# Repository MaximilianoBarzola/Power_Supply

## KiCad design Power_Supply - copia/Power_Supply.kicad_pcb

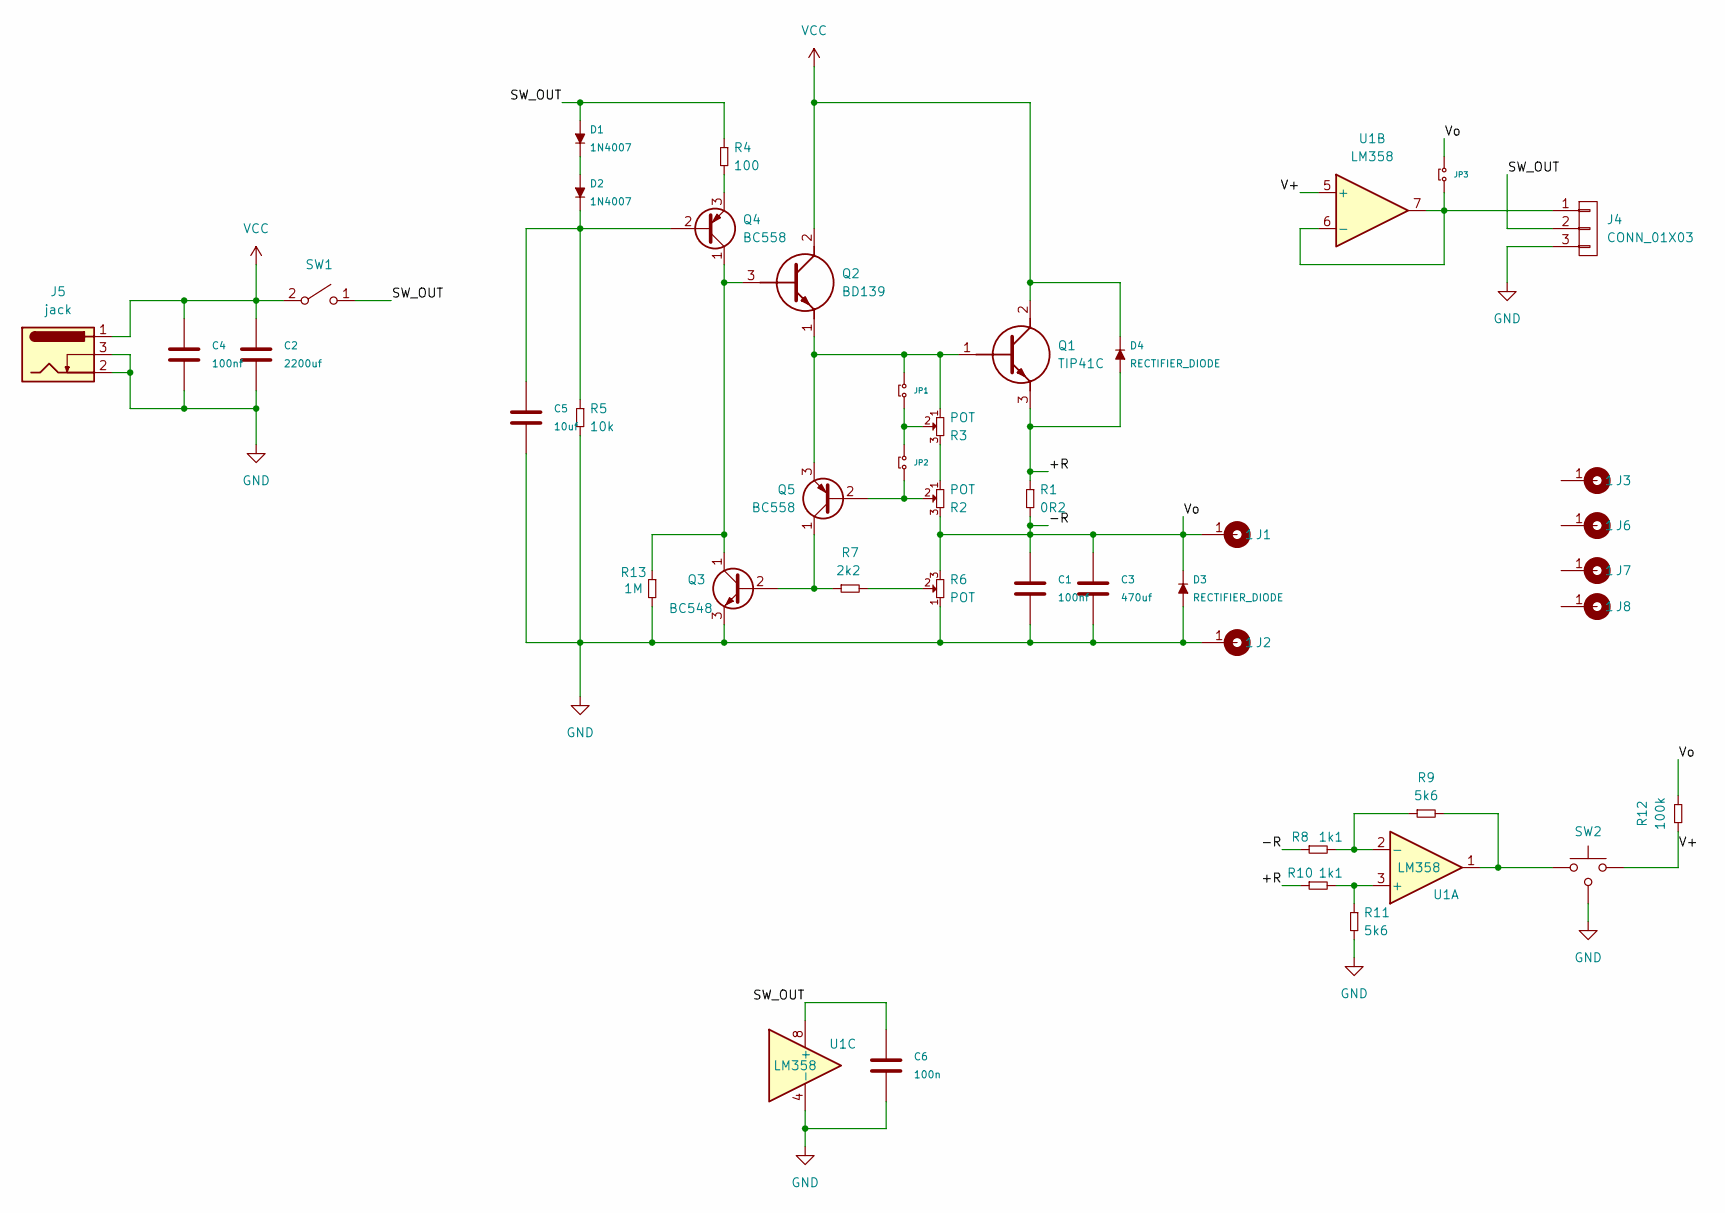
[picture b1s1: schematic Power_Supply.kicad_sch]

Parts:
C1, C4: 100nf; C_POL
C2: 2200uf; C_ELEC_15x12
C3: 470uf; C-ELEC
C5: 10uf; CAP_ELEC_5x11mm
C6: 100n; C_POL
D1, D2: 1N4007; DO-41
D3, D4: RECTIFIER_DIODE; DO-41
J1, J2: Cable_PAD; Cable_1,5mm
J3, J6, J7, J8: Cable_PAD; Separador_M3_10mm
J4: CONN_01X03; Pin_Header_3
J5: jack; Jack_hembra_DC_barrel
JP1, JP2, JP3: Jumper; JUMPER
Q1: TIP41C; TO-220-3_90; Manufacturer_Part_Number TIP41C; Mouser Part Number 512-TIP41C
Q2: BD139; TO-126-3_90; Manufacturer_Part_Number BD139; Mouser Part Number 863-BD139
Q3: BC548; to92
Q4, Q5: BC558; to92; Manufacturer_Part_Number BC558; Mouser Part Number 512-BC558
R1: 0R2; RESO_2W
R2, R6: POT; Pin_Header_3
R3: POT; TRIMER_V
R4: 100; RES0.3
R5: 10k; RES0.3
R7: 2k2; RES0.3
R8, R10: 1k1; RES0.3
R9, R11: 5k6; RES0.3
R12: 100k; RES0.3
R13: 1M; RES0.3
SW1: SW_SPST; Pin_Header_2
SW2: SW_Push; PUSH_SWITCH_THT_90
U1: LM358; DIP-8

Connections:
/+R: D4.1 (A), Q1.3 (E), R1.1, R10.1
/-R: C1.1, C3.1, D3.2 (K), J1.1, JP3.1 (A), R1.2, R2.3, R6.3, R8.1, R12.2
/SW_OUT: C6.1, D1.1 (A), J4.2, R4.1, SW1.1 (A), U1.8 (+)
/V+: R12.1, SW2.1, U1.5 (+)
GND: C1.2, C2.2, C3.2, C4.2, C5.2, C6.2, D3.1 (A), J2.1, J4.3, J5.2, J5.3, Q3.3 (E), R5.2, R6.1, R11.2, R13.2, SW2.3, U1.4 (-)
unnamed: D1.2 (K), D2.1 (A)
unnamed: C5.1, D2.2 (K), Q4.2 (B), R5.1
unnamed: J4.1, JP3.2 (B), U1.6 (-), U1.7
unnamed: JP1.1 (A), Q1.1 (B), Q2.1 (E), Q5.3 (E), R3.1
unnamed: JP1.2 (B), JP2.1 (A), R3.2
unnamed: JP2.2 (B), Q5.2 (B), R2.2
unnamed: Q2.3 (B), Q3.1 (C), Q4.1 (C), R13.1
unnamed: Q3.2 (B), Q5.1 (C), R7.1
unnamed: Q4.3 (E), R4.2
unnamed: R2.1, R3.3
unnamed: R6.2, R7.2
unnamed: R9.2, SW2.2, U1.1
unnamed: R10.2, R11.1, U1.3 (+)
unnamed: R8.2, R9.1, U1.2 (-)
VCC: C2.1, C4.1, D4.2 (K), J5.1, Q1.2 (C), Q2.2 (C), SW1.2 (B)

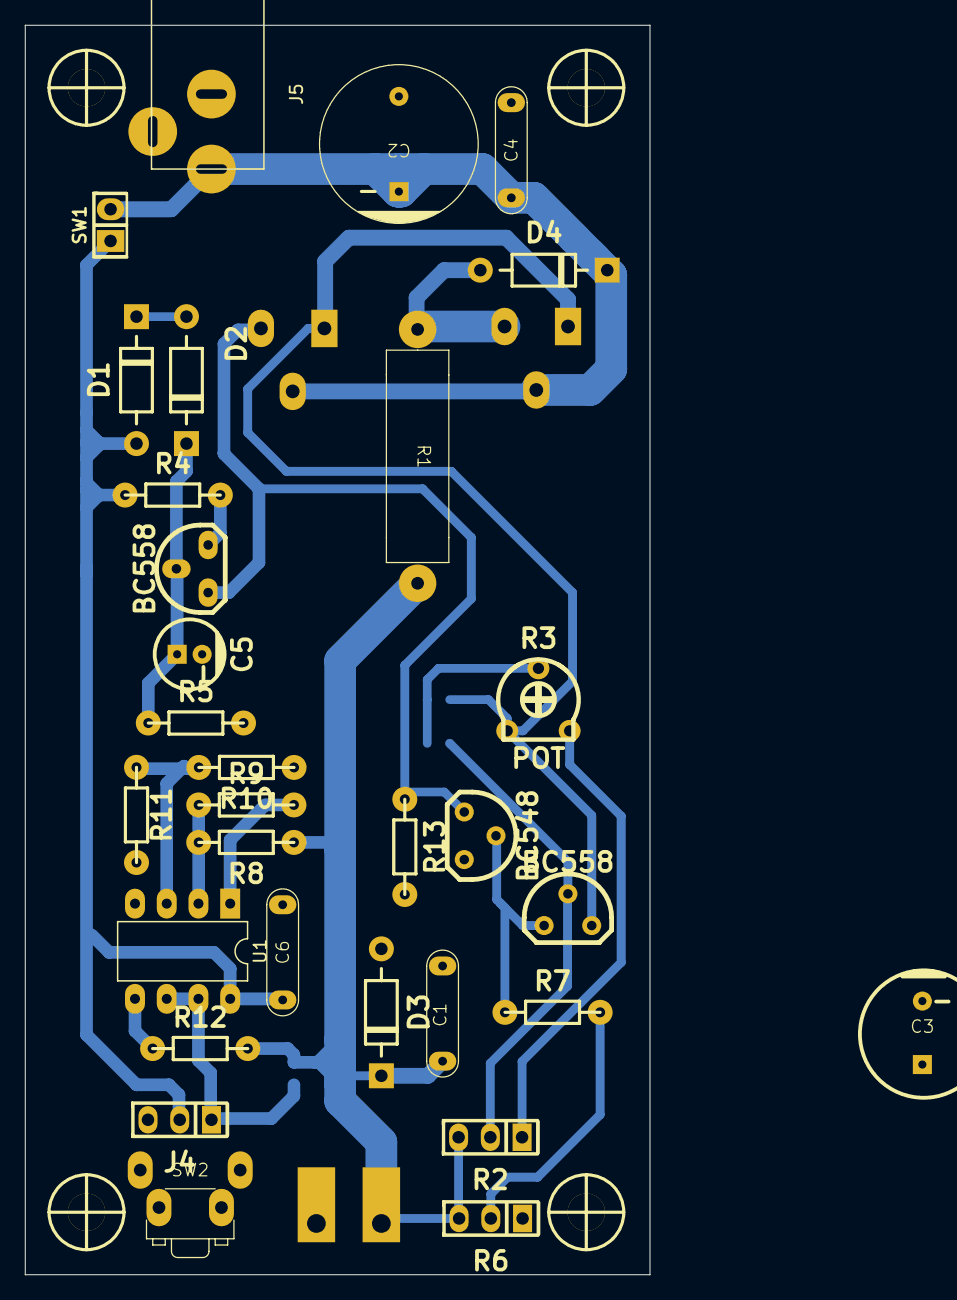
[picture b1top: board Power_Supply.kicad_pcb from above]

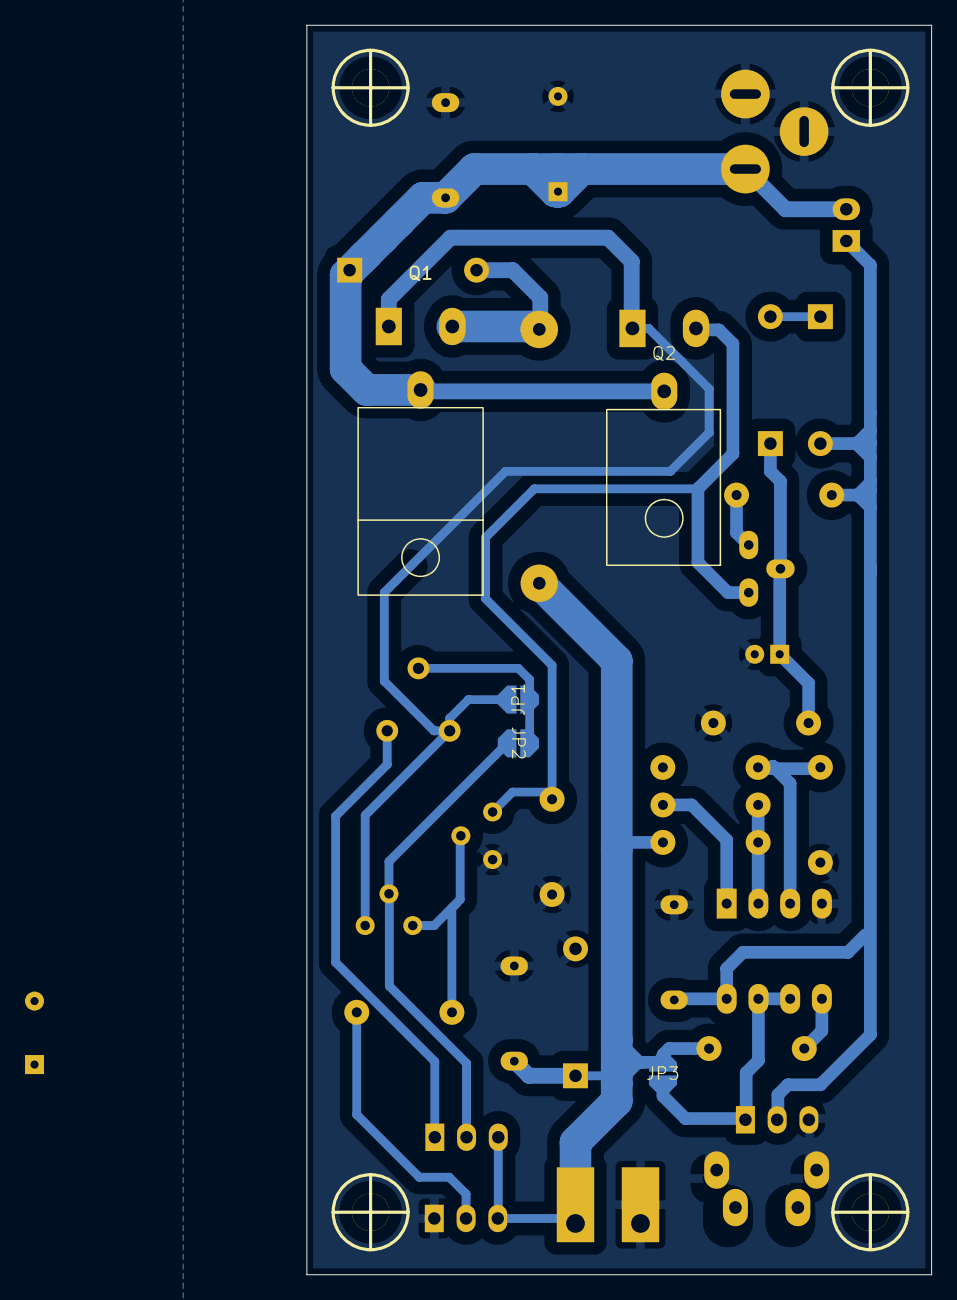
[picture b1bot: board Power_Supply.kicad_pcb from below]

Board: 2 copper layers, 50.0 x 100.0 mm, 42 parts (5 on the bottom side), 20 nets.

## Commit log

2024-08-09 new footprint
2024-08-29 PCB new
